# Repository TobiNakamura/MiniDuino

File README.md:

# MiniDuino
A minimalist arduino module featuring a ATmega328p, external clock, and 5v regulator with reverse polarity protection. 
Note unite does not have USART <-> USB capability.

# Programming
Connect Bus Pirate (red board) to MiniDuino.
	MISO -> PB4
	MOSI -> PB3
	CLK -> PB5
	CS -> RESET
	GND -> GND

Apply power to the MiniDuino. 
	9 volts -> Vin

Write Program in Arduino (or atmel studio). For pin numbering reference see Arduino_Uno_Rev3-schematic.pdf.
Export compiled hex file from Arduino IDE
	Sketch > Export Compiled Binary

Upload the hex file to MiniDuino using AVRDude
	$ sudo avrdude -c buspirate -P /dev/ttyUSB0 -p atmega328p -F -v -U flash:w:[name of file].hex

# Technical Details

The board was partially constructed to test the input polarity protection (up to 20v), voltage regulator (drop off 5.12v), and reset pin circuit (default pulled to 5v, button press pulls to GND).

MCU was drag soldered and the first blinky program is flashed. The factory default is for the MCU to use the internal RC oscillator, resulting in a very slow blinky.

Using AVRDude, fuse bits CKSEL[0..3] was changed from the default 0010 to 1111 for the external low power crystal oscilator.
avrdude -c usbtiny -p atmega328p -F -v -U lfuse:w:0xFF:m

Channel 1(yellow) is XTAL1, channel 2 (blue is XTAL2). Both waveforms are within spec. Just look at their stability...

There does however seem to be some stray inductance; mostlikely due to my bad soldering.

Done!

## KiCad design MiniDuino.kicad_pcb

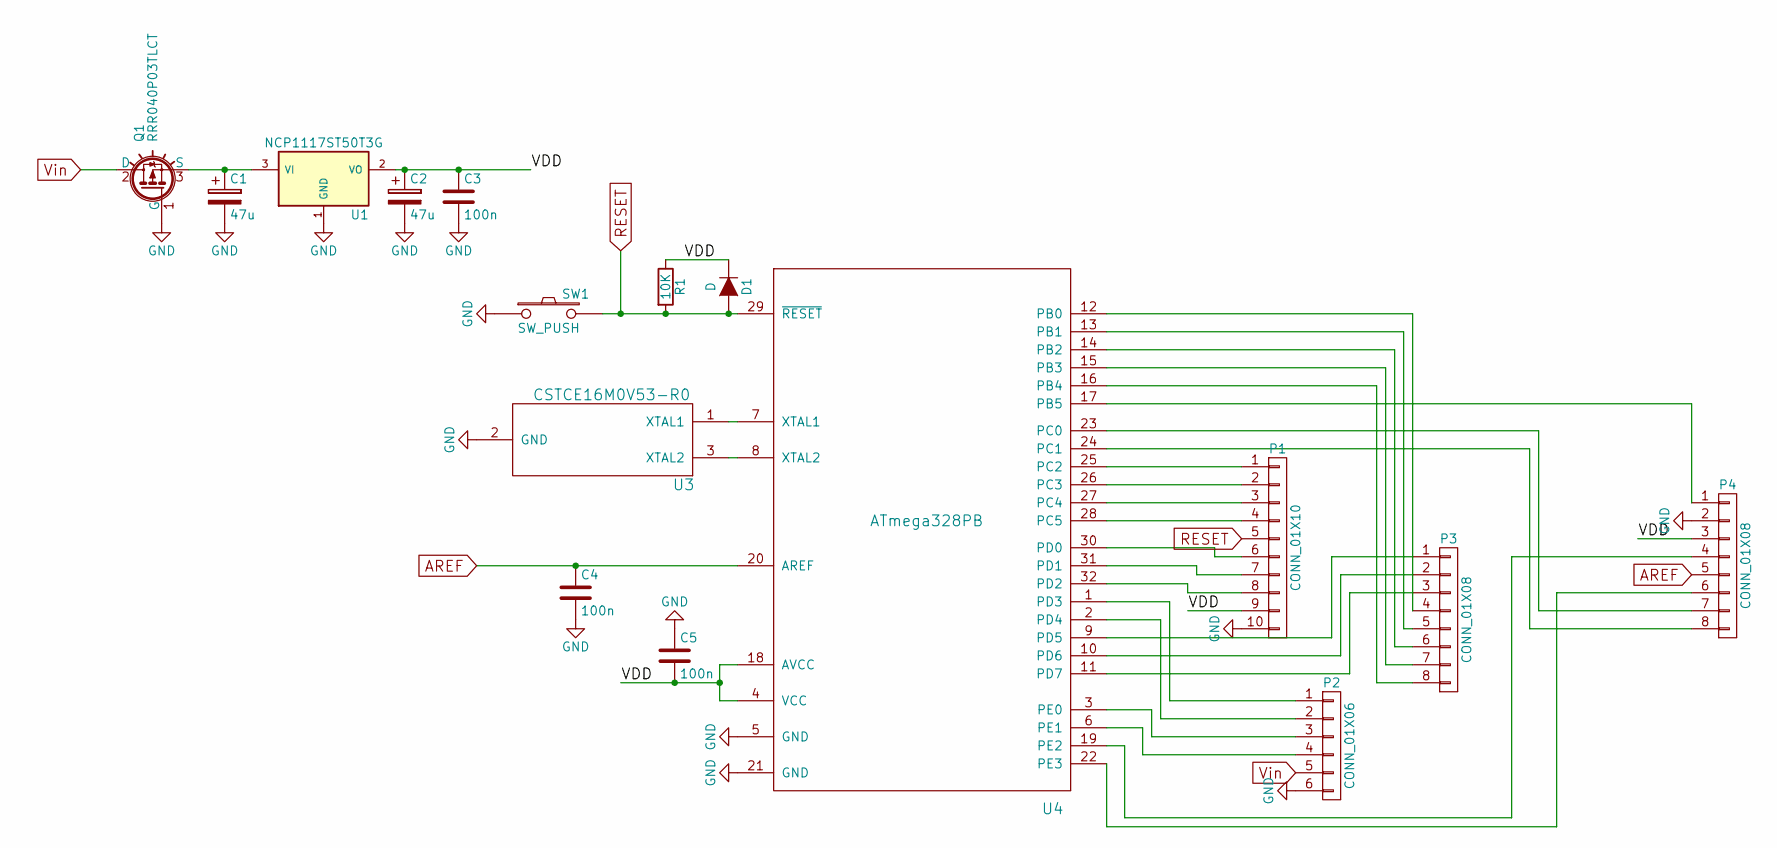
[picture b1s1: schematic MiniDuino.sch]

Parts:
C1, C2: 47u; C_Radial_D5_L11_P2
C3, C4, C5: 100n; C_1206_HandSoldering
D1: D; SMD-1206_Pol
P1: CONN_01X10; Pin_Header_Straight_1x10
P2: CONN_01X06; Pin_Header_Straight_1x06
P3, P4: CONN_01X08; Pin_Header_Straight_1x08
Q1: RRR040P03TLCT; RRR040P03
R1: 10K; R_1206_HandSoldering
SW1: SW_PUSH; PTS645
U1: NCP1117ST50T3G; SOT-223
U3: CSTCE16M0V53-R0
U4: ATmega328PB; TQFP-32_7x7mm_Pitch0.8mm

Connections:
/VDD: C2.1, C3.1, C5.2, D1.1 (K), P1.9, P4.3, R1.1, U1.2 (VO), U4.4 (VCC), U4.18 (AVCC)
AREF: C4.1, P4.5, U4.20 (AREF)
GND: C1.2, C2.2, C3.2, C4.2, C5.1, P1.10, P2.6, P4.2, Q1.1 (G), SW1.1, U1.1 (GND), U3.2 (GND), U4.5 (GND), U4.21 (GND); also elsewhere on the board
unnamed: C1.1, Q1.3 (S), U1.3 (VI)
unnamed: P1.1, U4.25 (PC2)
unnamed: P1.2, U4.26 (PC3)
unnamed: P1.3, U4.27 (PC4)
unnamed: P1.4, U4.28 (PC5)
unnamed: P1.6, U4.30 (PD0)
unnamed: P1.7, U4.31 (PD1)
unnamed: P1.8, U4.32 (PD2)
unnamed: P2.1, U4.1 (PD3)
unnamed: P2.2, U4.2 (PD4)
unnamed: P2.3, U4.3 (PE0)
unnamed: P2.4, U4.6 (PE1)
unnamed: P3.1, U4.9 (PD5)
unnamed: P3.2, U4.10 (PD6)
unnamed: P3.3, U4.11 (PD7)
unnamed: P3.4, U4.12 (PB0)
unnamed: P3.5, U4.13 (PB1)
unnamed: P3.6, U4.14 (PB2)
unnamed: P3.7, U4.15 (PB3)
unnamed: P3.8, U4.16 (PB4)
unnamed: P4.1, U4.17 (PB5)
unnamed: P4.4, U4.19 (PE2)
unnamed: P4.6, U4.22 (PE3)
unnamed: P4.7, U4.23 (PC0)
unnamed: P4.8, U4.24 (PC1)
unnamed: U3.1 (XTAL1), U4.7 (XTAL1)
unnamed: U3.3 (XTAL2), U4.8 (XTAL2)
RESET: D1.2 (A), P1.5, R1.2, SW1.2, U4.29 (~RESET); also elsewhere on the board
Vin: P2.5, Q1.2 (D)

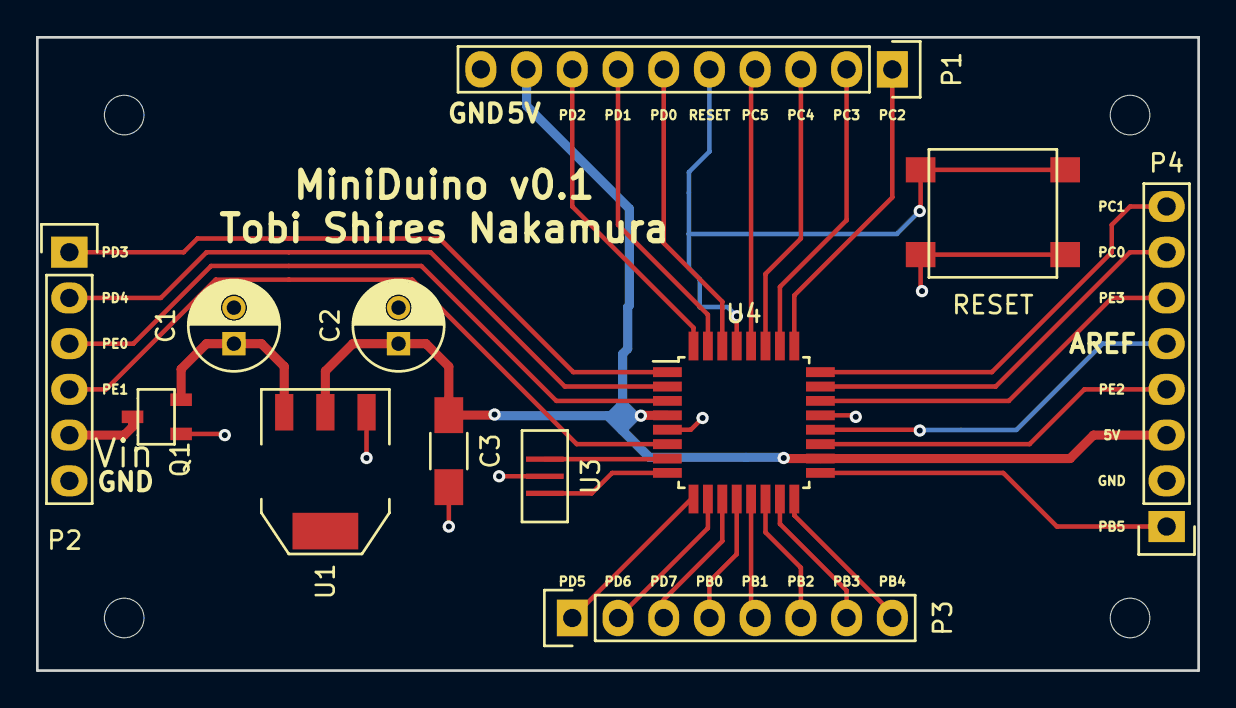
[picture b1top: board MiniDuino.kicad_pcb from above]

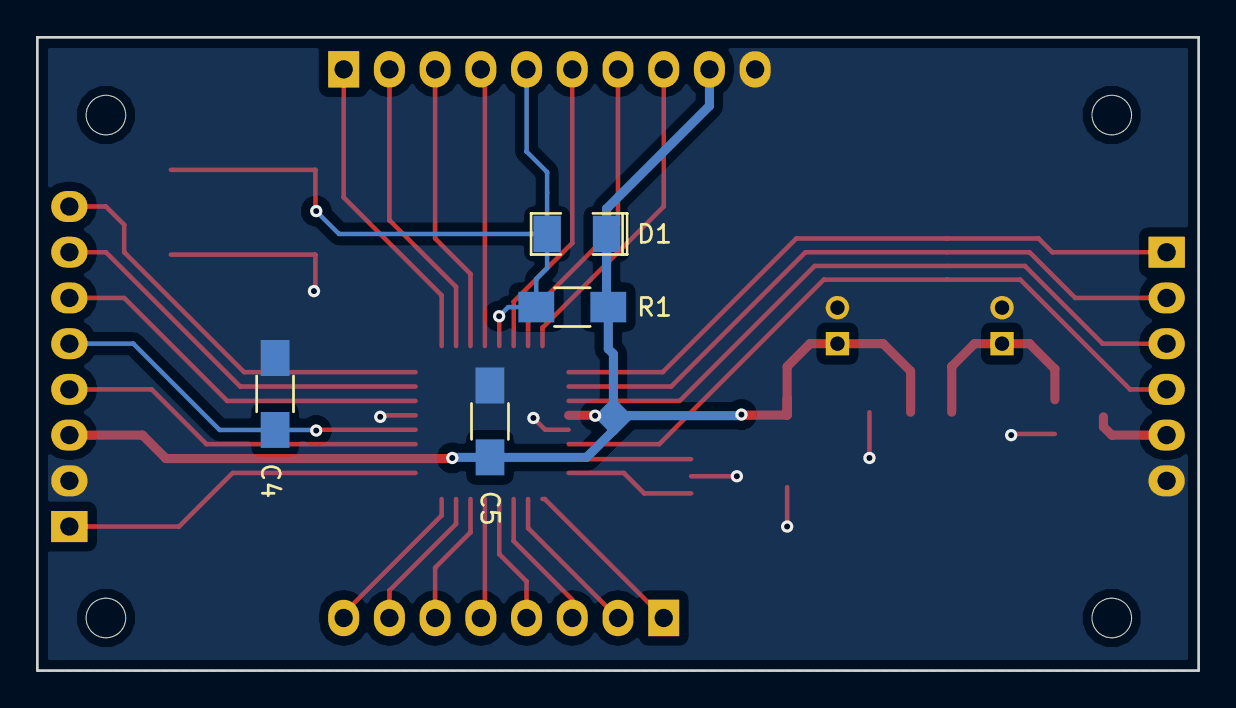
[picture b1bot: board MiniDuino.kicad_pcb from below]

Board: 2 copper layers, 64.5 x 35.2 mm, 16 parts (4 on the bottom side), 32 nets.

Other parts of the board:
RESET: SW_PUSH; PTS645

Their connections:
GND: RESET.1; also elsewhere on the board
RESET: RESET.2; also elsewhere on the board

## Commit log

2016-10-08 initial commit for version 0.1
2016-10-12 added images for documentation
2016-10-12 added readme and img for partially constructed board
2016-10-12 rotated sans-MCU.jpg
2016-10-12 cropped img of partially constructed board
2016-10-23 added readme and images for complete circuit
2016-10-24 added avrdude example
2016-10-24 added comment about bad soldering and inductance in clock signal
2016-10-24 added image of all 3 completed boards
2016-10-24 rotated img
2018-03-20 added programming instructions
